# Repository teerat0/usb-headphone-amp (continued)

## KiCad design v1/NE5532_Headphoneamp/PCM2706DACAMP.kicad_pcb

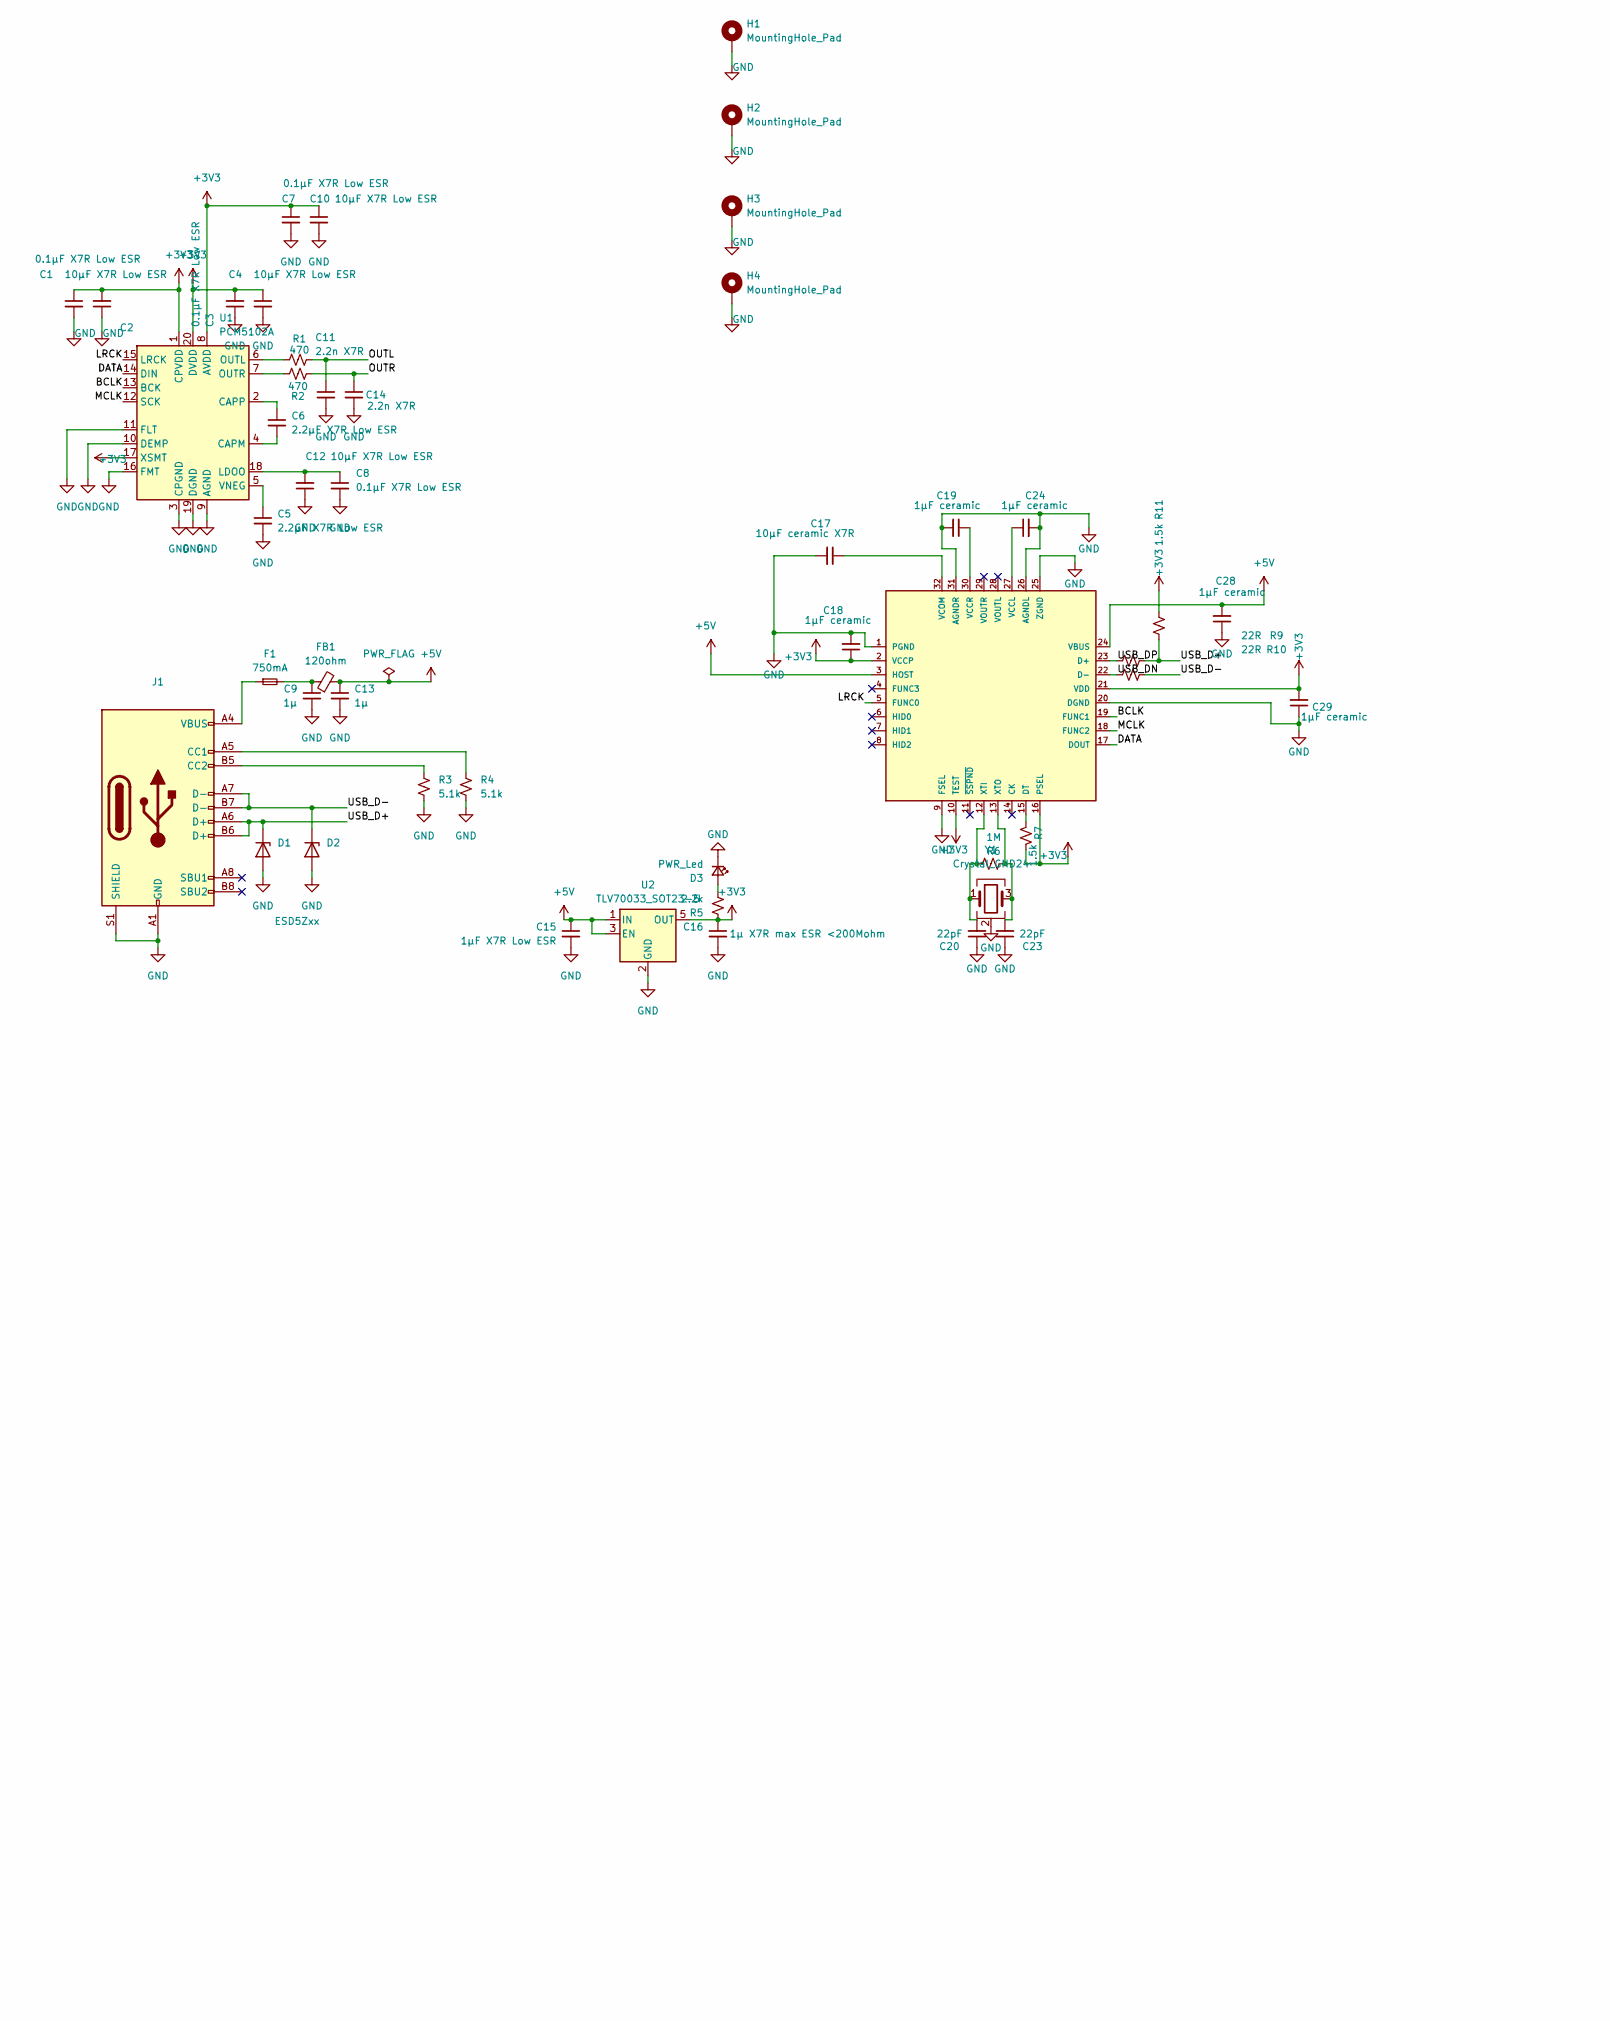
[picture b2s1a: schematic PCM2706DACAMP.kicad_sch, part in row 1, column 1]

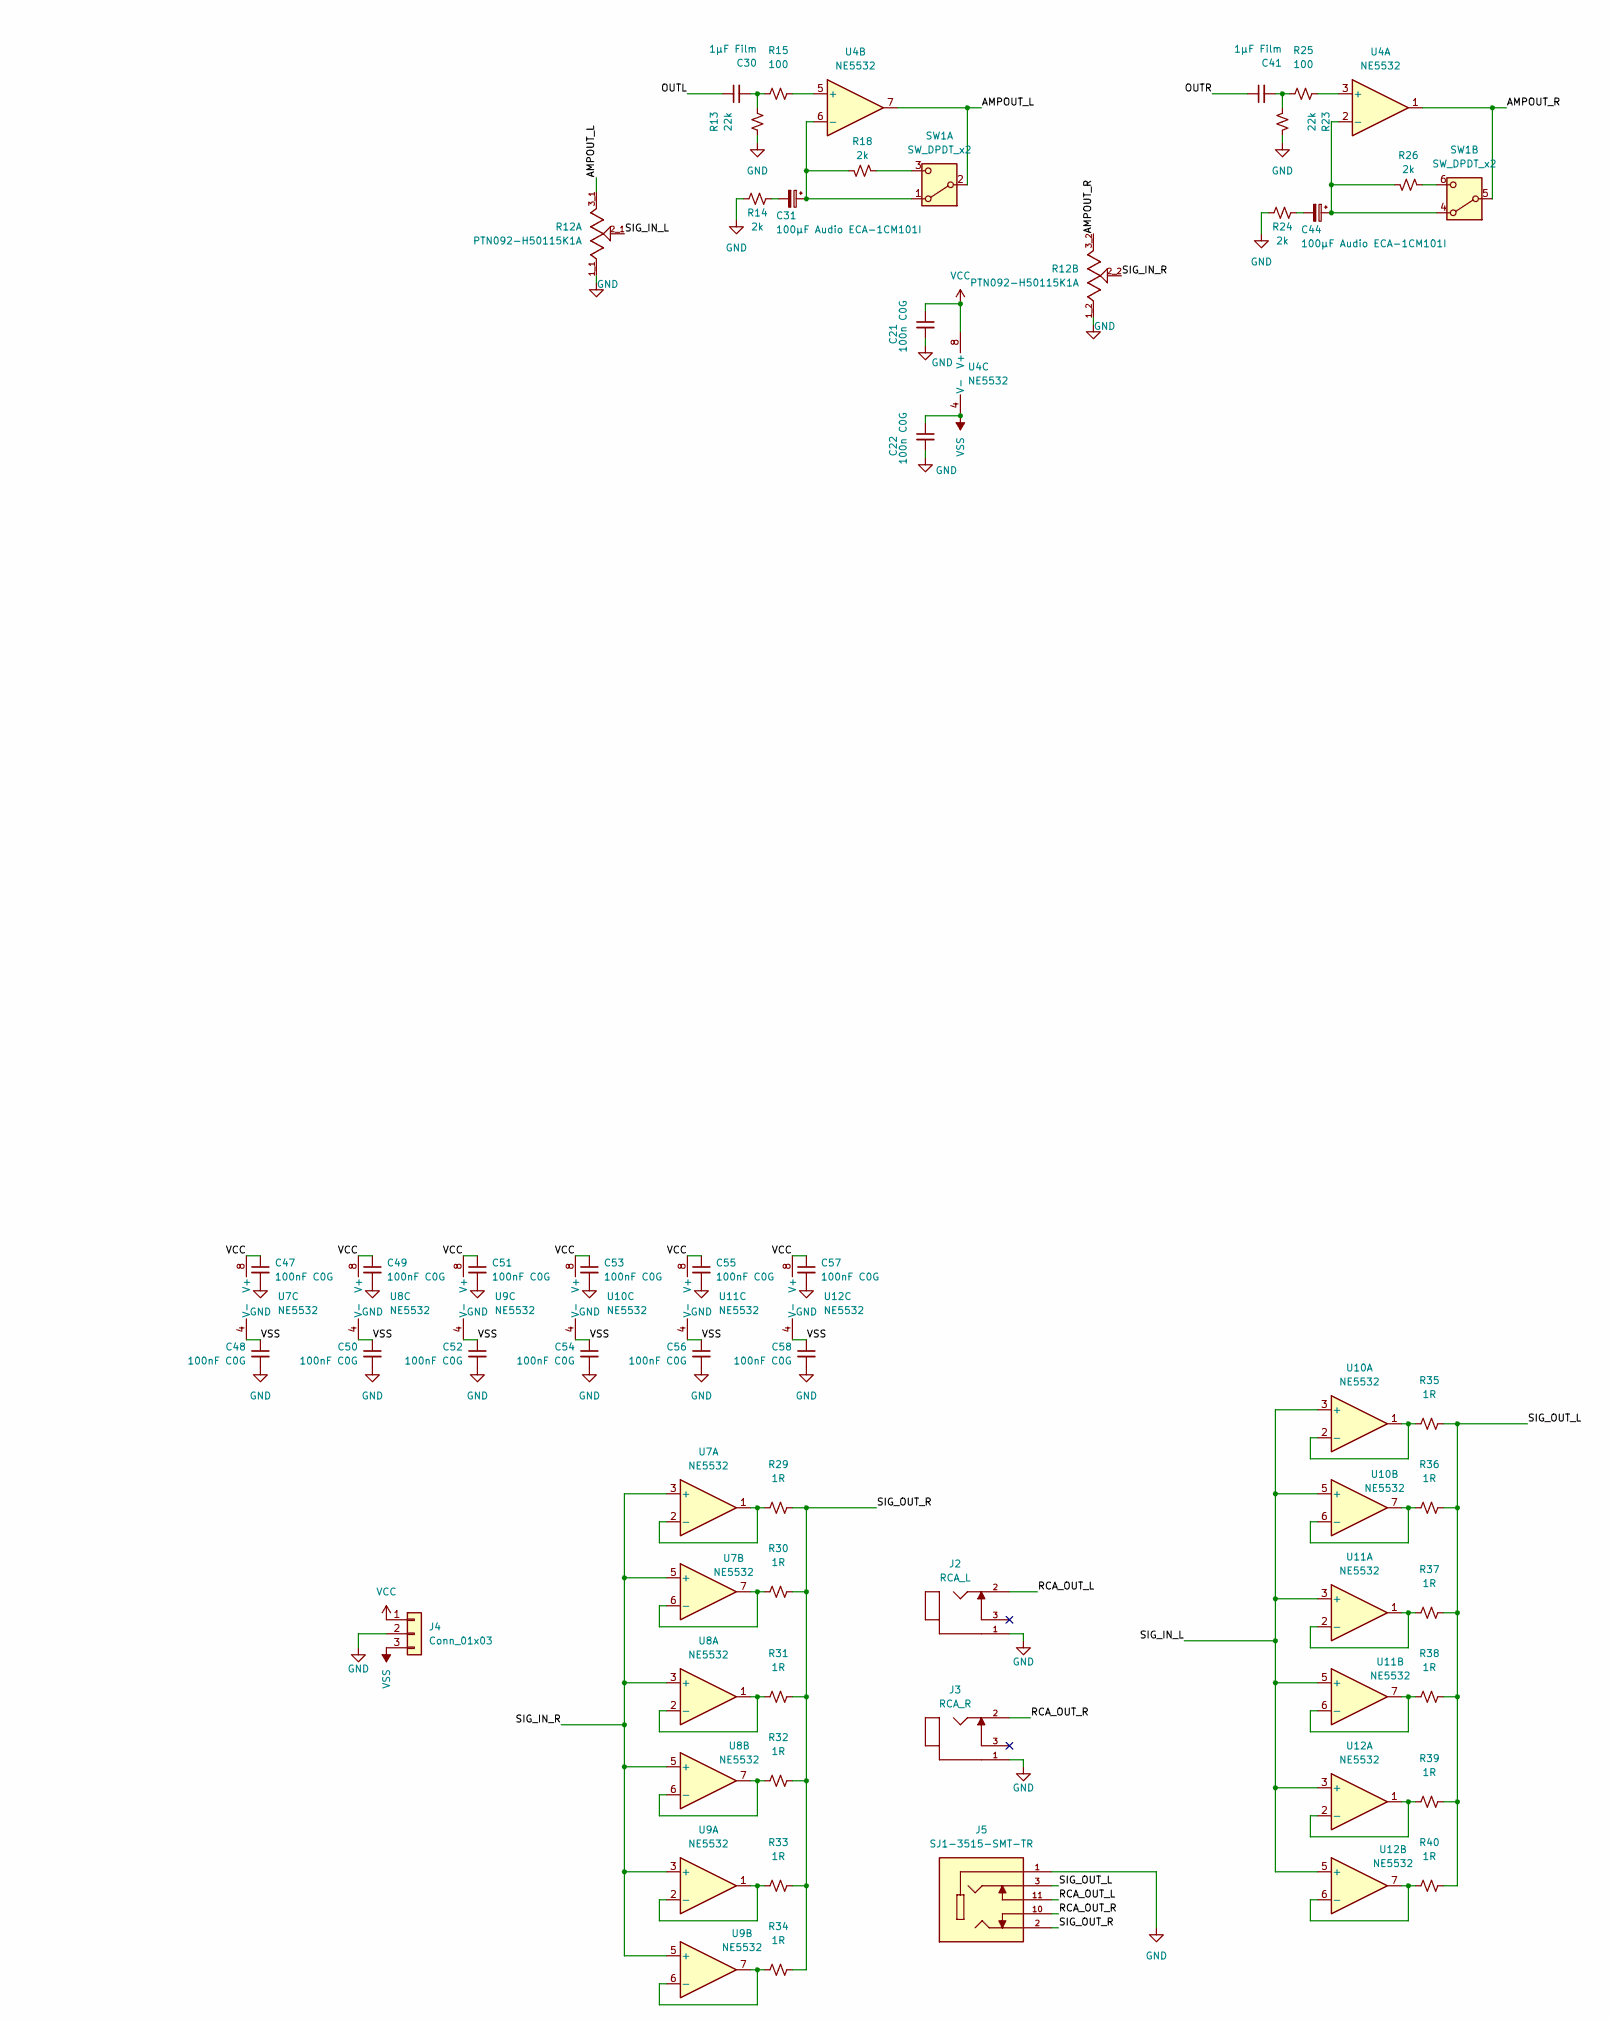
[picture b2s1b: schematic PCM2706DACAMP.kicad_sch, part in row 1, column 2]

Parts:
C1, C4, C10, C12: 10µF X7R Low ESR; C_0805_2012Metric
C2, C3, C7, C8: 0.1µF X7R Low ESR; C_0603_1608Metric
C5, C6: 2.2µF X7R Low ESR; C_0603_1608Metric
C9, C13: 1µ; C_0603_1608Metric
C11, C14: 2.2n X7R; C_0603_1608Metric
C15: 1µF X7R Low ESR; C_0603_1608Metric
C16: 1µ X7R max ESR <200Mohm; C_0603_1608Metric
C17: 10µF ceramic X7R; C_0805_2012Metric
C18, C19, C24, C28, C29: 1µF ceramic; C_0603_1608Metric
C20, C23: 22pF; C_0603_1608Metric
C21, C22: 100n C0G; C_0603_1608Metric
C30, C41: 1µF Film; C_Rect_L7.2mm_W6.0mm_P5.00mm
C31, C44: 100µF Audio ECA-1CM101I; CP_Radial_D5.0mm_P2.50mm
C47, C48, C49, C50, C51, C52, C53, C54, C55, C56, C57, C58: 100nF C0G; C_0603_1608Metric
D1, D2: ESD5Zxx; D_SOD-523
D3: PWR_Led; LED_0603_1608Metric
F1: 750mA; Fuse_0603_1608Metric
FB1: 120ohm; Ferrite_0603_1608Metric
H1, H2, H3, H4: MountingHole_Pad; MountingHole_3.2mm_M3_Pad_Via
IC1: PCM2706; TQFP-32_7x7mm_P0.8mm
J1: USB_C_Receptacle_USB2.0_16P; USB_C_Receptacle_GCT_USB4105-xx-A_16P_TopMnt_Horizontal
J2: RCA_L; SWITCHCRAFT_PJRAN1X1U01X; PARTREV A; DigiKey_Part_Number PJRAN1X1U01X-ND
J3: RCA_R; SWITCHCRAFT_PJRAN1X1U01X; PARTREV A; DigiKey_Part_Number PJRAN1X1U01X-ND
J4: Conn_01x03; JST_XH_B3B-XH-A_1x03_P2.50mm_Vertical
J5: SJ1-3515-SMT-TR; CUI_SJ1-3515-SMT-TR; PARTREV 1.08
R1, R2: 470; R_0603_1608Metric
R3, R4: 5.1k; R_0603_1608Metric
R5: 2.2k; R_0603_1608Metric
R6: 1M; R_0603_1608Metric
R7, R11: 1.5k; R_0603_1608Metric
R9, R10: 22R; R_0603_1608Metric
R12: PTN092-H50115K1A; TRIM_PTN092-H50115K1A; PARTREV 1.01; DigiKey_Part_Number 2223-PTN092-H50115K1A-ND
R13, R23: 22k; R_0603_1608Metric
R14, R24: 2k; R_0603_1608Metric
R15, R25: 100; R_0603_1608Metric
R18, R26: 2k; R_0805_2012Metric
R29, R30, R31, R32, R33, R34, R35, R36, R37, R38, R39, R40: 1R; R_0805_2012Metric
SW1: SW_DPDT_x2; SW_E-Switch_EG2219_DPDT_Angled
U1: PCM5102A; TSSOP-20_4.4x6.5mm_P0.65mm
U2: TLV70033_SOT23-5; SOT-23-5
U4, U7, U8, U9, U10, U11, U12: NE5532; NE5532_SOCKETED
Y1: Crystal_GND24; Crystal_SMD_Abracon_ABM3C-4Pin_5.0x3.2mm

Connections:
+3V3: C1.1, C2.2, C3.2, C4.1, C7.1, C10.1, C16.1, C18.1, C29.2, IC1.2 (VCCP), IC1.10 (TEST), IC1.16 (PSEL), IC1.21 (VDD), R5.1, R7.2, R11.1, U1.1 (CPVDD), U1.8 (AVDD), U1.17 (XSMT), U1.20 (DVDD), U2.5 (OUT)
+5V: C13.1, C15.1, C28.2, FB1.2, IC1.3 (HOST), IC1.24 (VBUS), U2.1 (IN), U2.3 (EN)
/AMPOUT_L: R12.3_1, SW1.2 (B), U4.7
/AMPOUT_R: R12.3_2, SW1.5 (B), U4.1
/BCLK: IC1.19 (FUNC1), U1.13 (BCK)
/DATA: IC1.17 (DOUT), U1.14 (DIN)
/LRCK: IC1.5 (FUNC0), U1.15 (LRCK)
/MCLK: IC1.18 (FUNC2), U1.12 (SCK)
/OUTL: C11.1, C30.1, R1.2
/OUTR: C14.1, C41.1, R2.2
/RCA_OUT_L: J2.2, J5.11
/RCA_OUT_R: J3.2, J5.10
/SIG_IN_L: R12.2_1, U10.3 (+), U10.5 (+), U11.3 (+), U11.5 (+), U12.3 (+), U12.5 (+)
/SIG_IN_R: R12.2_2, U7.3 (+), U7.5 (+), U8.3 (+), U8.5 (+), U9.3 (+), U9.5 (+)
/SIG_OUT_L: J5.3, R35.2, R36.2, R37.2, R38.2, R39.2, R40.2
/SIG_OUT_R: J5.2, R29.2, R30.2, R31.2, R32.2, R33.2, R34.2
/USB_D+: D1.1 (K), J1.A6 (D+), J1.B6 (D+), R9.1, R11.2
/USB_D-: D2.1 (K), J1.A7 (D-), J1.B7 (D-), R10.1
/USB_DN: IC1.22 (D-), R10.2
/USB_DP: IC1.23 (D+), R9.2
GND: C1.2, C2.1, C3.1, C4.2, C5.2, C7.2, C8.1, C9.2, C10.2, C11.2, C12.2, C13.2, C14.2, C15.2, C16.2, C17.2, C18.2, C19.2, C20.1, C21.2, C22.2, C23.1, C24.2, C28.1, C29.1, C47.2, C48.2, C49.2, C50.2, C51.2, C52.2, C53.2, C54.2, C55.2, C56.2, C57.2, C58.2, D1.2 (A), D2.2 (A), D3.1 (K), H1.1, H2.1, H3.1, H4.1, IC1.1 (PGND), IC1.9 (FSEL), IC1.20 (DGND), IC1.25 (ZGND), IC1.26 (AGNDL), IC1.31 (AGNDR), J1.A1 (GND), J1.A12 (GND), J1.B1 (GND), J1.B12 (GND), J1.S1 (SHIELD), J2.1, J3.1, J4.2, J5.1, R3.2, R4.2, R12.1_1, R12.1_2, R13.1, R14.1, R23.1, R24.1, U1.3 (CPGND), U1.9 (AGND), U1.10 (DEMP), U1.11 (FLT), U1.16 (FMT), U1.19 (DGND), U2.2 (GND), Y1.2 (G), Y1.4 (G)
unnamed: C9.1, F1.2, FB1.1
unnamed: C30.2, R13.2, R15.1
unnamed: C31.2, R14.2
unnamed: C41.2, R23.2, R25.1
unnamed: C44.2, R24.2
unnamed: D3.2 (A), R5.2
unnamed: F1.1, J1.A4 (VBUS), J1.A9 (VBUS), J1.B4 (VBUS), J1.B9 (VBUS)
unnamed: IC1.15 (DT), R7.1
unnamed: C24.1, IC1.27 (VCCL)
unnamed: C19.1, IC1.30 (VCCR)
unnamed: C17.1, IC1.32 (VCOM)
unnamed: C20.2, IC1.12 (XTI), R6.2, Y1.1
unnamed: C23.2, IC1.13 (XTO), R6.1, Y1.3
unnamed: J1.A5 (CC1), R4.1
unnamed: J1.B5 (CC2), R3.1
unnamed: C31.1, R18.2, SW1.1 (A), U4.6 (-)
unnamed: R18.1, SW1.3 (C)
unnamed: C44.1, R26.2, SW1.4 (A), U4.2 (-)
unnamed: R26.1, SW1.6 (C)
unnamed: C6.2, U1.4 (CAPM)
unnamed: C6.1, U1.2 (CAPP)
unnamed: C8.2, C12.1, U1.18 (LDOO)
unnamed: R1.1, U1.6 (OUTL)
unnamed: R2.1, U1.7 (OUTR)
unnamed: C5.1, U1.5 (VNEG)
unnamed: R25.2, U4.3 (+)
unnamed: R15.2, U4.5 (+)
unnamed: R29.1, U7.1, U7.2 (-)
unnamed: R30.1, U7.6 (-), U7.7
unnamed: R31.1, U8.1, U8.2 (-)
unnamed: R32.1, U8.6 (-), U8.7
unnamed: R33.1, U9.1, U9.2 (-)
unnamed: R34.1, U9.6 (-), U9.7
unnamed: R35.1, U10.1, U10.2 (-)
unnamed: R36.1, U10.6 (-), U10.7
unnamed: R37.1, U11.1, U11.2 (-)
unnamed: R38.1, U11.6 (-), U11.7
unnamed: R39.1, U12.1, U12.2 (-)
unnamed: R40.1, U12.6 (-), U12.7
VCC: C21.1, C47.1, C49.1, C51.1, C53.1, C55.1, C57.1, J4.1, U4.8 (V+), U7.8 (V+), U8.8 (V+), U9.8 (V+), U10.8 (V+), U11.8 (V+), U12.8 (V+)
VSS: C22.1, C48.1, C50.1, C52.1, C54.1, C56.1, C58.1, J4.3, U4.4 (V-), U7.4 (V-), U8.4 (V-), U9.4 (V-), U10.4 (V-), U11.4 (V-), U12.4 (V-)

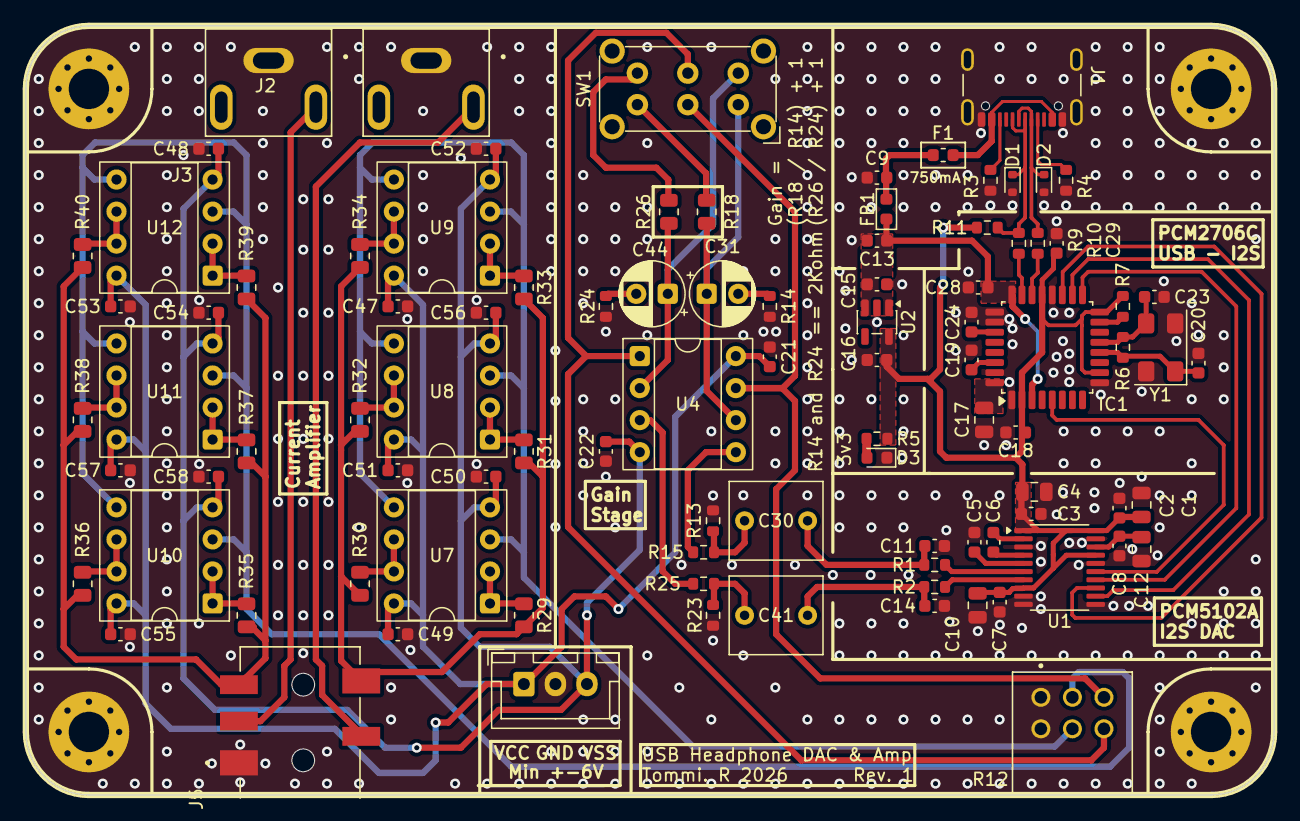
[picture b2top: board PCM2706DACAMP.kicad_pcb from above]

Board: 2 copper layers, 99.0 x 61.0 mm, 99 parts (0 on the bottom side), 62 nets.

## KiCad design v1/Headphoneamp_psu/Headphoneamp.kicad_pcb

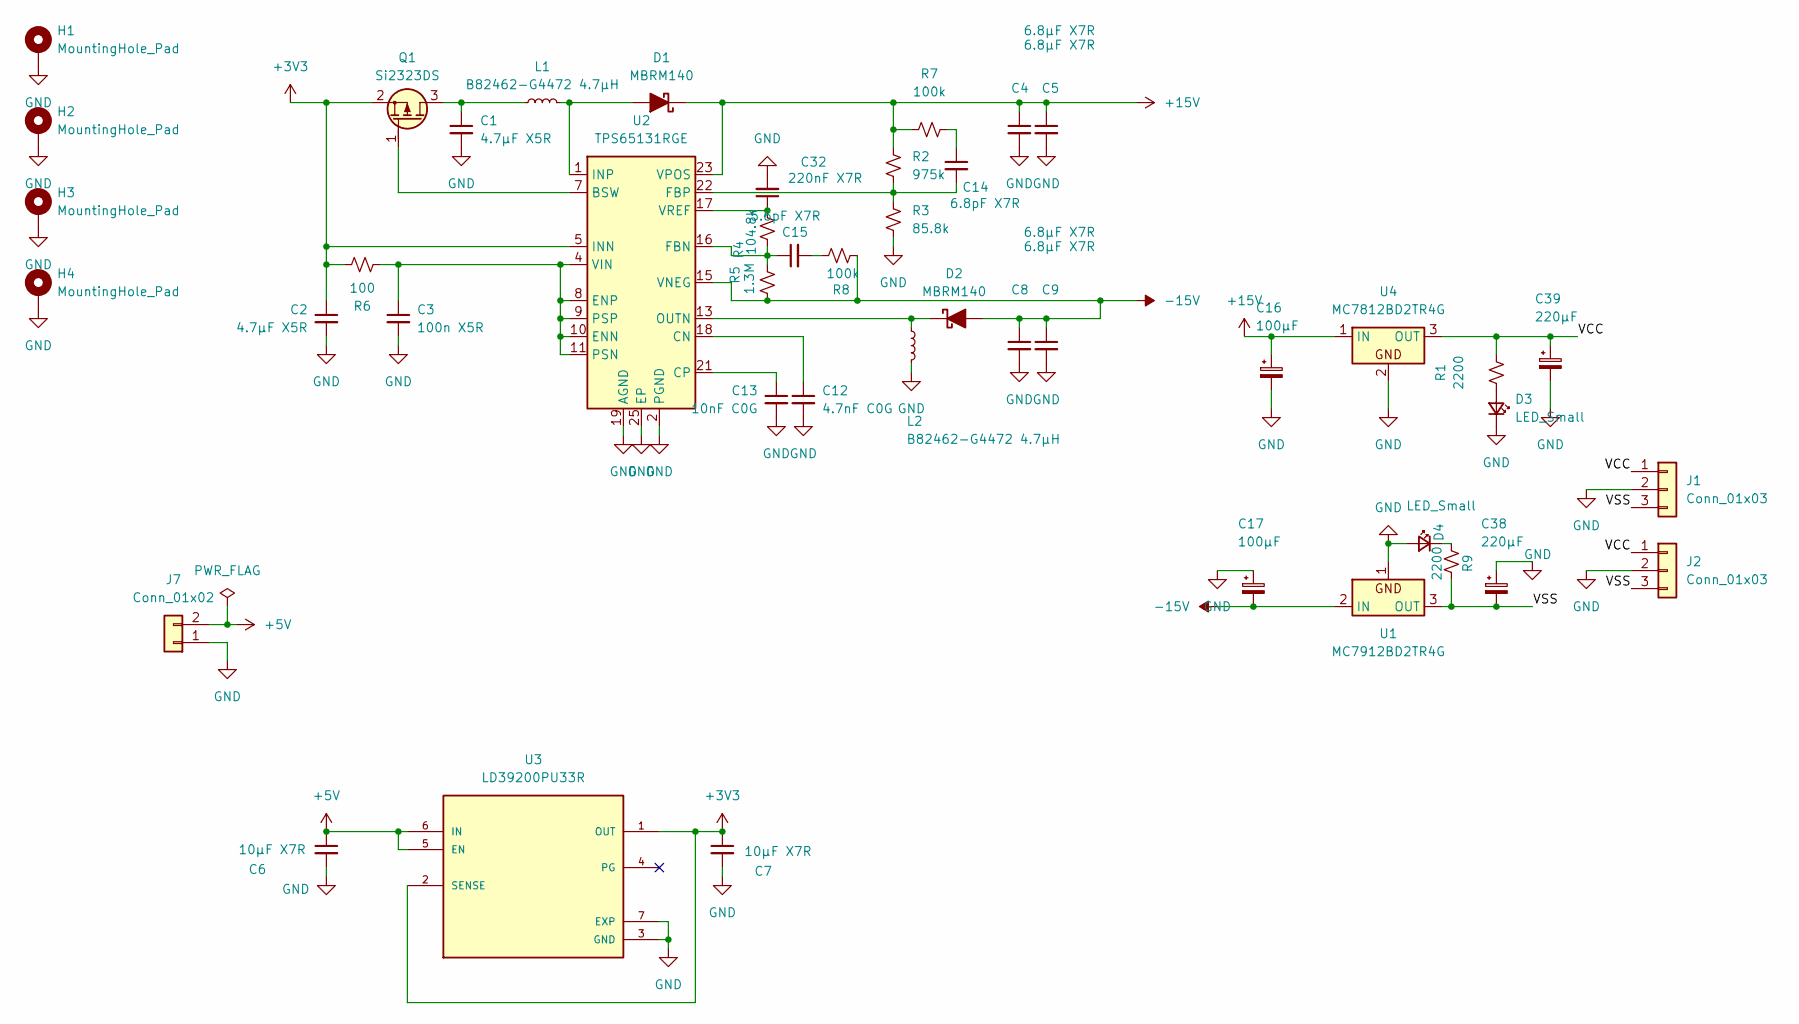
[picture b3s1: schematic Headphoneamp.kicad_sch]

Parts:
C1, C2: 4.7µF X5R; C_0603_1608Metric
C3: 100n X5R; C_0603_1608Metric
C4, C5, C8, C9: 6.8µF X7R; C_0603_1608Metric
C6, C7: 10µF X7R; C_0603_1608Metric
C12: 4.7nF C0G; C_0603_1608Metric
C13: 10nF C0G; C_0603_1608Metric
C14: 6.8pF X7R; C_0603_1608Metric
C15: 5.6pF X7R; C_0603_1608Metric
C16, C17: 100µF; CP_Radial_D8.0mm_P3.50mm
C32: 220nF X7R; C_0603_1608Metric
C38, C39: 220µF; CP_Radial_D8.0mm_P3.50mm
D1, D2: MBRM140; D_Powermite_AK
D3, D4: LED_Small; LED_0603_1608Metric
H1, H2, H3, H4: MountingHole_Pad; MountingHole_3.2mm_M3_Pad_Via
J1, J2: Conn_01x03; JST_XH_B3B-XH-A_1x03_P2.50mm_Vertical
J7: Conn_01x02; JST_XH_B2B-XH-A_1x02_P2.50mm_Vertical
L1, L2: B82462-G4472 4.7µH; L_6.3x6.3_H3
Q1: Si2323DS; SOT-23
R1, R9: 2200; R_0603_1608Metric
R2: 975k; R_0603_1608Metric
R3: 85.8k; R_0603_1608Metric
R4: 104.8k; R_0603_1608Metric
R5: 1.3M; R_0603_1608Metric
R6: 100; R_0603_1608Metric
R7, R8: 100k; R_0603_1608Metric
U1: MC7912BD2TR4G; TO-263-2
U2: TPS65131RGE; VQFN-24-1EP_4x4mm_P0.5mm_EP2.45x2.45mm_ThermalVias
U3: LD39200PU33R; SON95P300X300X100-7N; PARTREV 3
U4: MC7812BD2TR4G; TO-263-2

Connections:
+3V3: C2.1, C7.1, Q1.2 (S), R6.2, U2.5 (INN), U2.6 (INN), U3.1 (OUT), U3.2 (SENSE)
+5V: C6.1, J7.2, U3.5 (EN), U3.6 (IN)
+15V: C4.1, C5.1, C16.1, D1.1 (K), R2.1, R7.1, U2.23 (VPOS), U4.1 (IN)
-15V: C8.1, C9.1, C17.2, D2.2 (A), R5.2, R8.2, U1.2 (IN), U2.15 (VNEG)
/VCC: C39.1, J1.1, J2.1, R1.2, U4.3 (OUT)
/VSS: C38.2, J1.3, J2.3, R9.2, U1.3 (OUT)
GND: C1.2, C2.2, C3.2, C4.2, C5.2, C6.2, C7.2, C8.2, C9.2, C12.2, C13.2, C16.2, C17.1, C32.2, C38.1, C39.2, D3.1 (K), D4.2 (A), H1.1, H2.1, H3.1, H4.1, J1.2, J2.2, J7.1, L2.2, R3.2, U1.1, U2.2 (PGND), U2.3 (PGND), U2.19 (AGND), U2.25 (EP), U3.3 (GND), U3.7 (EXP), U4.2
unnamed: C14.1, R7.2
unnamed: C15.2, R8.1
unnamed: D1.2 (A), L1.2, U2.1 (INP), U2.24 (INP)
unnamed: D2.1 (K), L2.1, U2.13 (OUTN), U2.14 (OUTN)
unnamed: D3.2 (A), R1.1
unnamed: D4.1 (K), R9.1
unnamed: C1.1, L1.1, Q1.3 (D)
unnamed: Q1.1 (G), U2.7 (BSW)
unnamed: C12.1, U2.18 (CN)
unnamed: C13.1, U2.21 (CP)
unnamed: C3.1, R6.1, U2.4 (VIN), U2.8 (ENP), U2.9 (PSP), U2.10 (ENN), U2.11 (PSN)
unnamed: C15.1, R4.2, R5.1, U2.16 (FBN)
unnamed: C14.2, R2.2, R3.1, U2.22 (FBP)
unnamed: C32.1, R4.1, U2.17 (VREF)

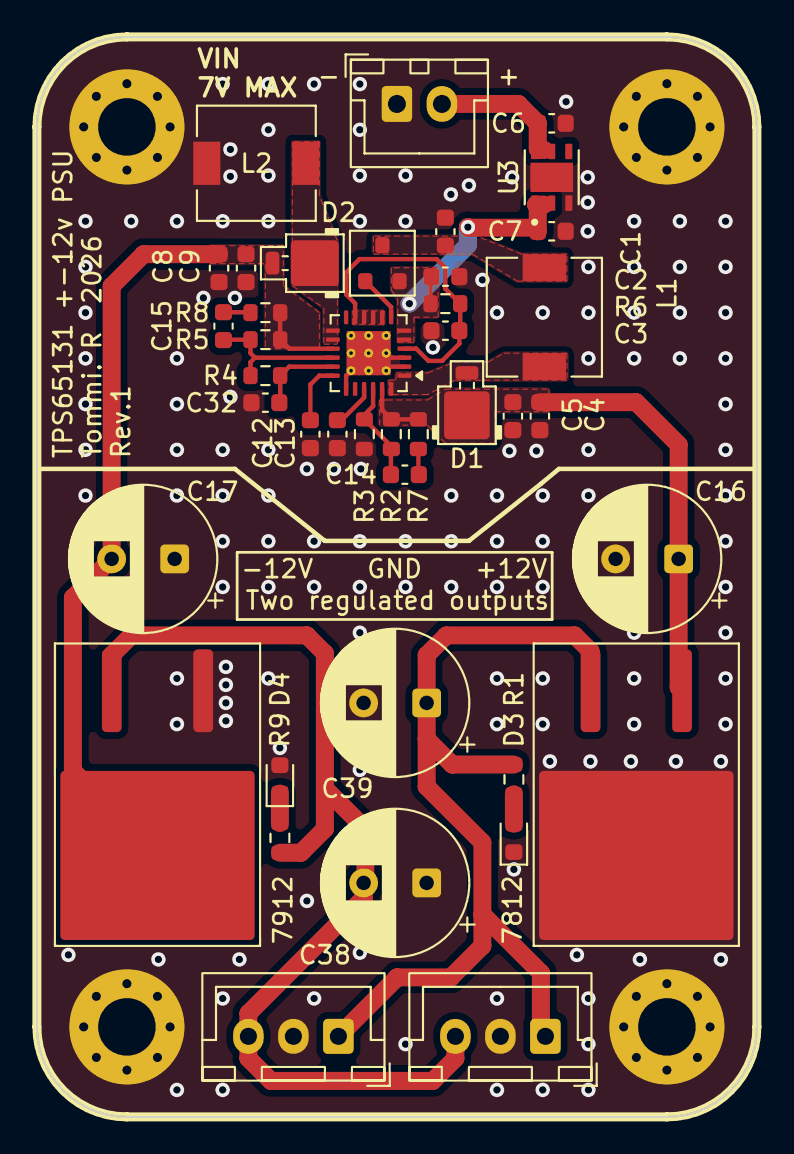
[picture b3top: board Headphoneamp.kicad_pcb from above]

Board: 2 copper layers, 40.0 x 60.0 mm, 45 parts (0 on the bottom side), 21 nets.

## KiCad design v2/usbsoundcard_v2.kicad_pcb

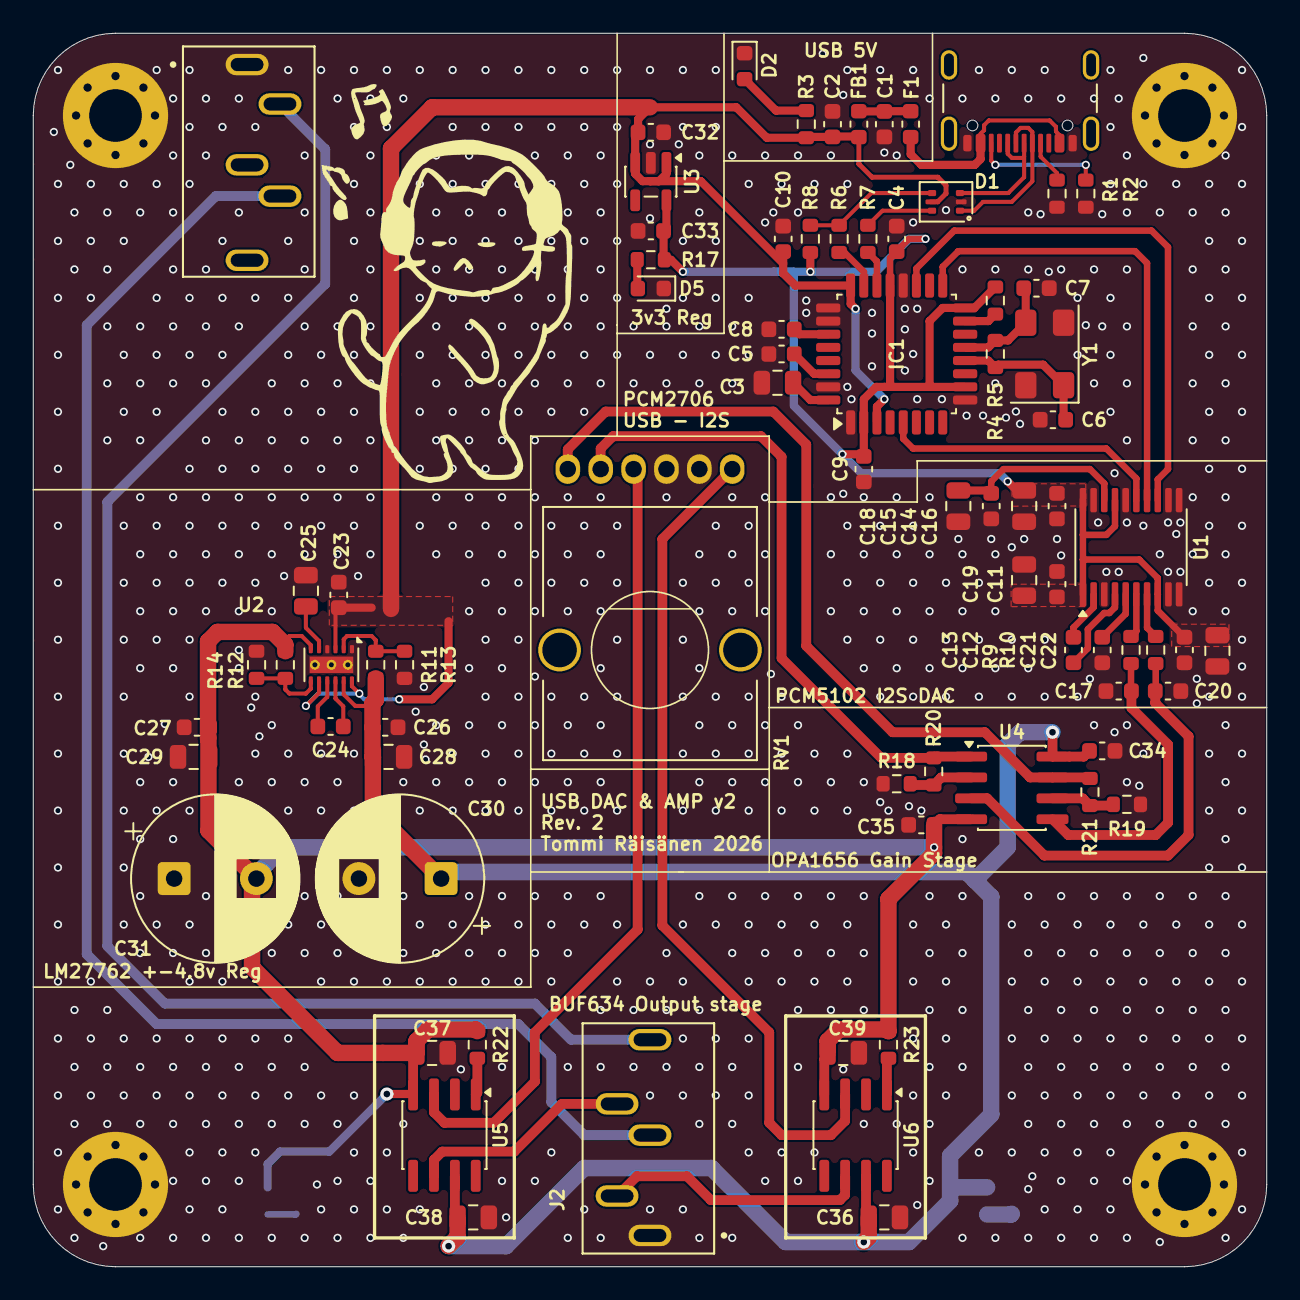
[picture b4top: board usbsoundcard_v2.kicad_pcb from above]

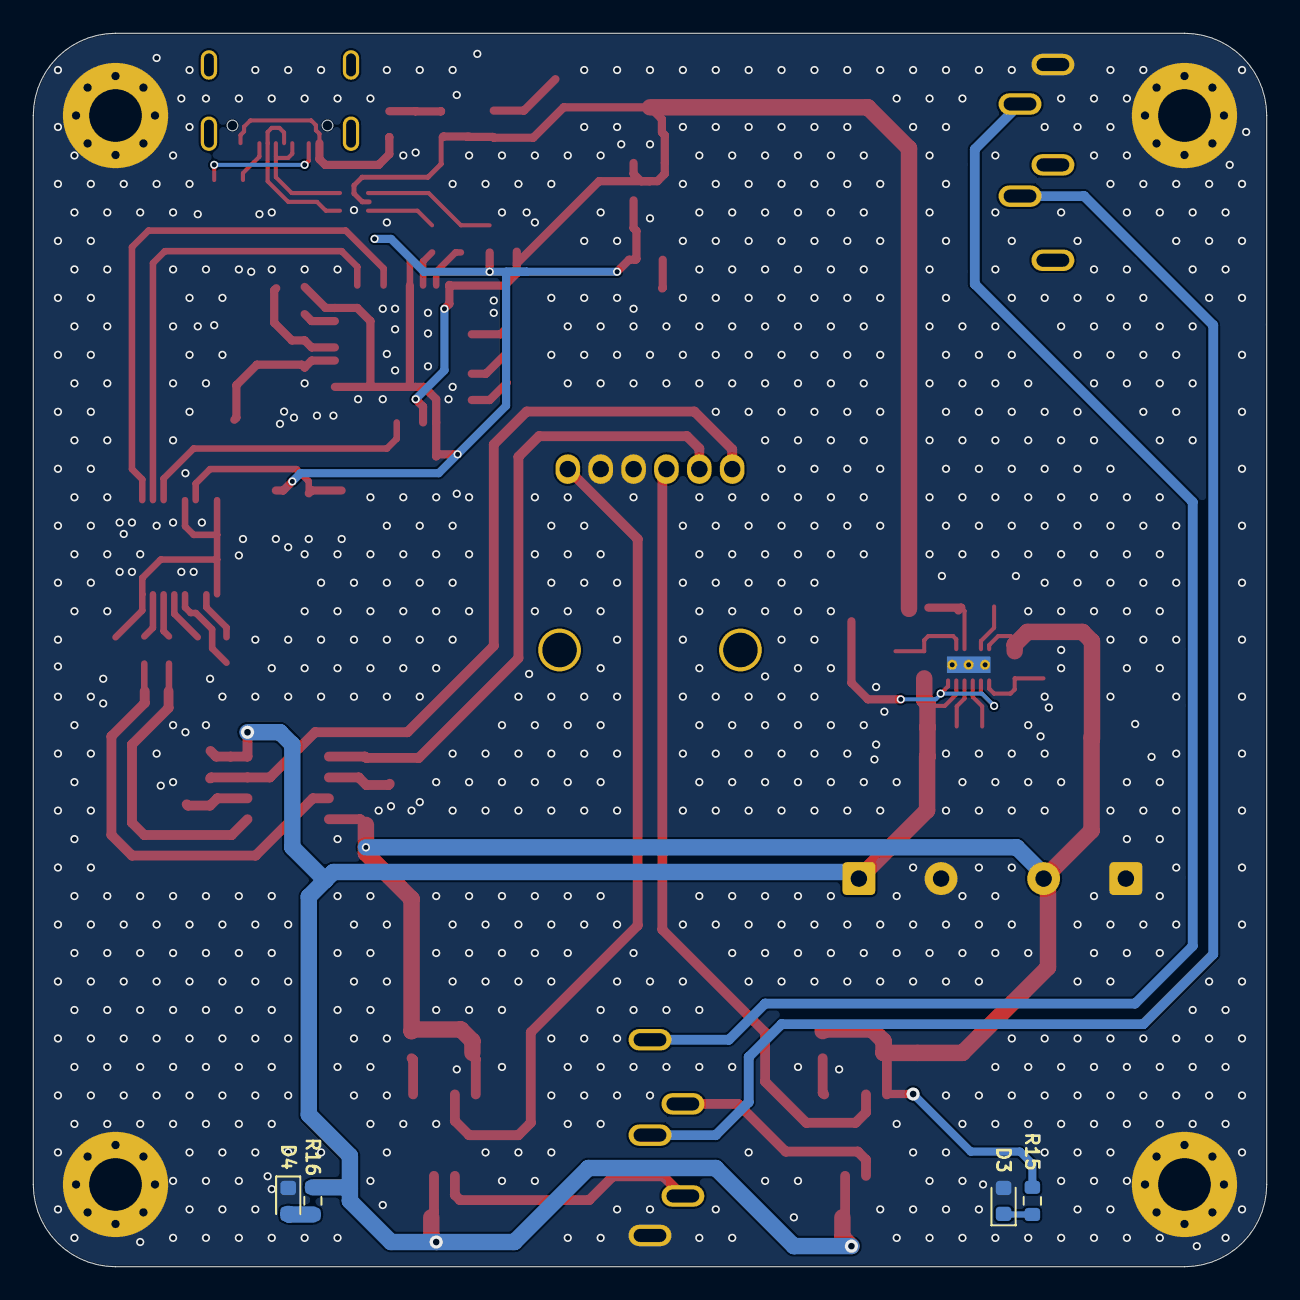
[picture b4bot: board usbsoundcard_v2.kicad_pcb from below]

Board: 2 copper layers, 75.0 x 75.0 mm, 85 parts (4 on the bottom side), 53 nets.

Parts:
C1, C2, C26, C27, C32, C33: 1µF; C_0603_1608Metric
C3: 10µF ceramic X7R; C_0805_2012Metric
C4, C5, C8, C9, C10: 1µF ceramic; C_0603_1608Metric
C6, C7: 22pF; C_0603_1608Metric
C11, C15, C16, C21, C34, C35: 100nF; C_0603_1608Metric
C12, C13: 2.2µF; C_0603_1608Metric
C14, C18, C19, C22, C25, C36, C37, C38, C39: 10µF; C_0805_2012Metric
C17, C20: 2n2; C_0603_1608Metric
C23: 4.7µF; C_0603_1608Metric
C24: 1µf; C_0603_1608Metric
C28, C29: 10µf; C_0805_2012Metric
C30, C31: DNP; CP_Radial_D10.0mm_P5.00mm
D1: USBLC6-2P6; SOT-666
D2, D3, D4, D5: LED; LED_0603_1608Metric
F1: 500mA-750mA; Fuse_0603_1608Metric
FB1: 120ohm; L_0603_1608Metric
H1, H2, H3, H4: MountingHole_Pad; MountingHole_3.2mm_M3_Pad_Via
IC1: PCM2706; TQFP-32_7x7mm_P0.8mm
J1: USB_C_Receptacle_USB2.0_16P; USB_C_Receptacle_GCT_USB4105-xx-A_16P_TopMnt_Horizontal
J2, J3: SJ1-3535N; CUI_SJ1-3535N
R1, R2: 5k1; R_0603_1608Metric
R3, R15, R16, R17: 4K7; R_0603_1608Metric
R4: 1M; R_0603_1608Metric
R5, R8: 1.5k; R_0603_1608Metric
R6, R7: 22R; R_0603_1608Metric
R9, R10: 470; R_0603_1608Metric
R11: 168k; R_0603_1608Metric
R12: 165k; R_0603_1608Metric
R13, R14: 56k; R_0603_1608Metric
R18, R19: 4k7; R_0603_1608Metric
R20, R21: 2k2; R_0603_1608Metric
R22, R23: 0-330; R_0603_1608Metric
RV1: VOL_POT; RK12L12
U1: PCM5102A; TSSOP-20_4.4x6.5mm_P0.65mm
U2: LM27762; WSON-12-1EP_3x2mm_P0.5mm_EP1x2.65_ThermalVias
U3: TLV70033_SOT23-5; SOT-23-5
U4: OPA1656ID; SOIC-8_3.9x4.9mm_P1.27mm
U5, U6: BUF634AxD; SOIC-8_3.9x4.9mm_P1.27mm
Y1: Crystal_GND24; Crystal_SMD_Abracon_ABM3C-4Pin_5.0x3.2mm

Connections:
3V3: C4.1, C9.2, C11.1, C14.1, C16.1, C19.1, C21.1, C22.1, C33.1, IC1.2 (VCCP), IC1.10 (TEST), IC1.16 (PSEL), IC1.21 (VDD), R5.2, R8.1, R17.2, U1.1 (CPVDD), U1.8 (AVDD), U1.17 (XSMT), U1.20 (DVDD), U3.5 (OUT)
/USB - I2S - DAC/USBC_D+: D1.4 (L2), R6.1, R8.2
/USB - I2S - DAC/USBC_D-: D1.6 (L1), R7.1
AMP_OUT_L: J2.2, U6.6
AMP_OUT_R: J2.3, U5.6
AMP_VCC: C26.1, C28.1, C30.1, C34.1, C36.1, C38.1, R11.1, R16.2, U2.11 (OUT+), U4.8 (V+), U5.7 (V+), U6.7 (V+)
AMP_VSS: C27.1, C29.1, C31.2, C35.1, C37.1, C39.1, R12.2, R15.2, R22.1, R23.1, U2.6 (OUT-), U4.4 (V-), U5.4 (V-), U6.4 (V-)
BCLK: IC1.19 (FUNC1), U1.13 (BCK)
DAC_OUTL: C17.1, R9.2, U4.5 (+)
DAC_OUTR: C20.1, R10.2, U4.3 (+)
DOUT: IC1.17 (DOUT), U1.14 (DIN)
GND: C1.2, C2.2, C3.2, C4.2, C5.2, C6.1, C7.1, C8.2, C9.1, C10.1, C11.2, C12.2, C14.2, C15.2, C16.2, C17.2, C18.2, C19.2, C20.2, C21.2, C22.2, C23.2, C25.2, C26.2, C27.2, C28.2, C29.2, C30.2, C31.1, C32.2, C33.2, C34.2, C35.2, C36.2, C37.2, C38.2, C39.2, D1.2 (VN), D2.1 (K), D3.2 (A), D4.1 (K), D5.1 (K), H1.1 (1_1), H2.1 (1_1), H3.1 (1_1), H4.1 (1_1), IC1.1 (PGND), IC1.9 (FSEL), IC1.20 (DGND), IC1.25 (ZGND), IC1.26 (AGNDL), IC1.31 (AGNDR), J1.A1 (GND), J1.A12 (GND), J1.B1 (GND), J1.B12 (GND), J2.1, J3.1, R1.2, R2.1, R13.2, R14.2, R18.1, R19.1, RV1.1, RV1.4, U1.3 (CPGND), U1.9 (AGND), U1.10 (DEMP), U1.11 (FLT), U1.12 (SCK), U1.16 (FMT), U1.19 (DGND), U2.1 (PGOOD), U2.4 (GND), U2.13 (PAD), U3.2 (GND), Y1.2 (G), Y1.4 (G)
GS_OUT_L: R21.2, RV1.6, U4.7
GS_OUT_R: R20.2, RV1.3, U4.1
LRCLK: IC1.5 (FUNC0), U1.15 (LRCK)
unnamed: C1.1, F1.2, FB1.1
unnamed: D1.1 (L1), J1.A7 (D-), J1.B7 (D-)
unnamed: D1.3 (L2), J1.A6 (D+), J1.B6 (D+)
unnamed: D2.2 (A), R3.1
unnamed: D3.1 (K), R15.1
unnamed: D4.2 (A), R16.1
unnamed: D5.2 (A), R17.1
unnamed: F1.1, J1.A4 (VBUS), J1.A9 (VBUS), J1.B4 (VBUS), J1.B9 (VBUS)
unnamed: IC1.23 (D+), R6.2
unnamed: IC1.22 (D-), R7.2
unnamed: IC1.15 (DT), R5.1
unnamed: C8.1, IC1.27 (VCCL)
unnamed: C5.1, IC1.30 (VCCR)
unnamed: C3.1, IC1.32 (VCOM)
unnamed: C6.2, IC1.12 (XTI), R4.2, Y1.1
unnamed: C7.2, IC1.13 (XTO), R4.1, Y1.3
unnamed: J1.A5 (CC1), R1.1
unnamed: J1.B5 (CC2), R2.2
unnamed: J2.4, J3.2
unnamed: J2.5, J3.3
unnamed: C13.2, U1.4 (CAPM)
unnamed: C13.1, U1.2 (CAPP)
unnamed: C15.1, C18.1, U1.18 (LDOO)
unnamed: R9.1, U1.6 (OUTL)
unnamed: R10.1, U1.7 (OUTR)
unnamed: C12.1, U1.5 (VNEG)
unnamed: C24.1, U2.10 (C+)
unnamed: C24.2, U2.9 (C-)
unnamed: C25.1, U2.5 (CP)
unnamed: R11.2, R13.1, U2.2 (FB+)
unnamed: R12.1, R14.1, U2.7 (FB-)
unnamed: R18.2, R20.1, U4.2 (-)
unnamed: R19.2, R21.1, U4.6 (-)
unnamed: R22.2, U5.1 (BW)
unnamed: RV1.2, U5.3 (V_{IN})
unnamed: R23.2, U6.1 (BW)
unnamed: RV1.5, U6.3 (V_{IN})
VBUS_Filtered: C2.1, C10.2, C23.1, C32.1, D1.5 (VP), FB1.2, IC1.3 (HOST), IC1.24 (VBUS), R3.2, U2.3 (VIN), U2.8 (EN-), U2.12 (EN+), U3.1 (IN), U3.3 (EN)
